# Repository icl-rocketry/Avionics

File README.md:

# Avionics
The main repository for hardware and software assosciated with the Ricardo Avionics Ecosystem. The goal of this project is to develop a generic highly configurable and powerful rocket avionics system which can accomodate many different rocket designs with differing propulsion systems as well as staging.

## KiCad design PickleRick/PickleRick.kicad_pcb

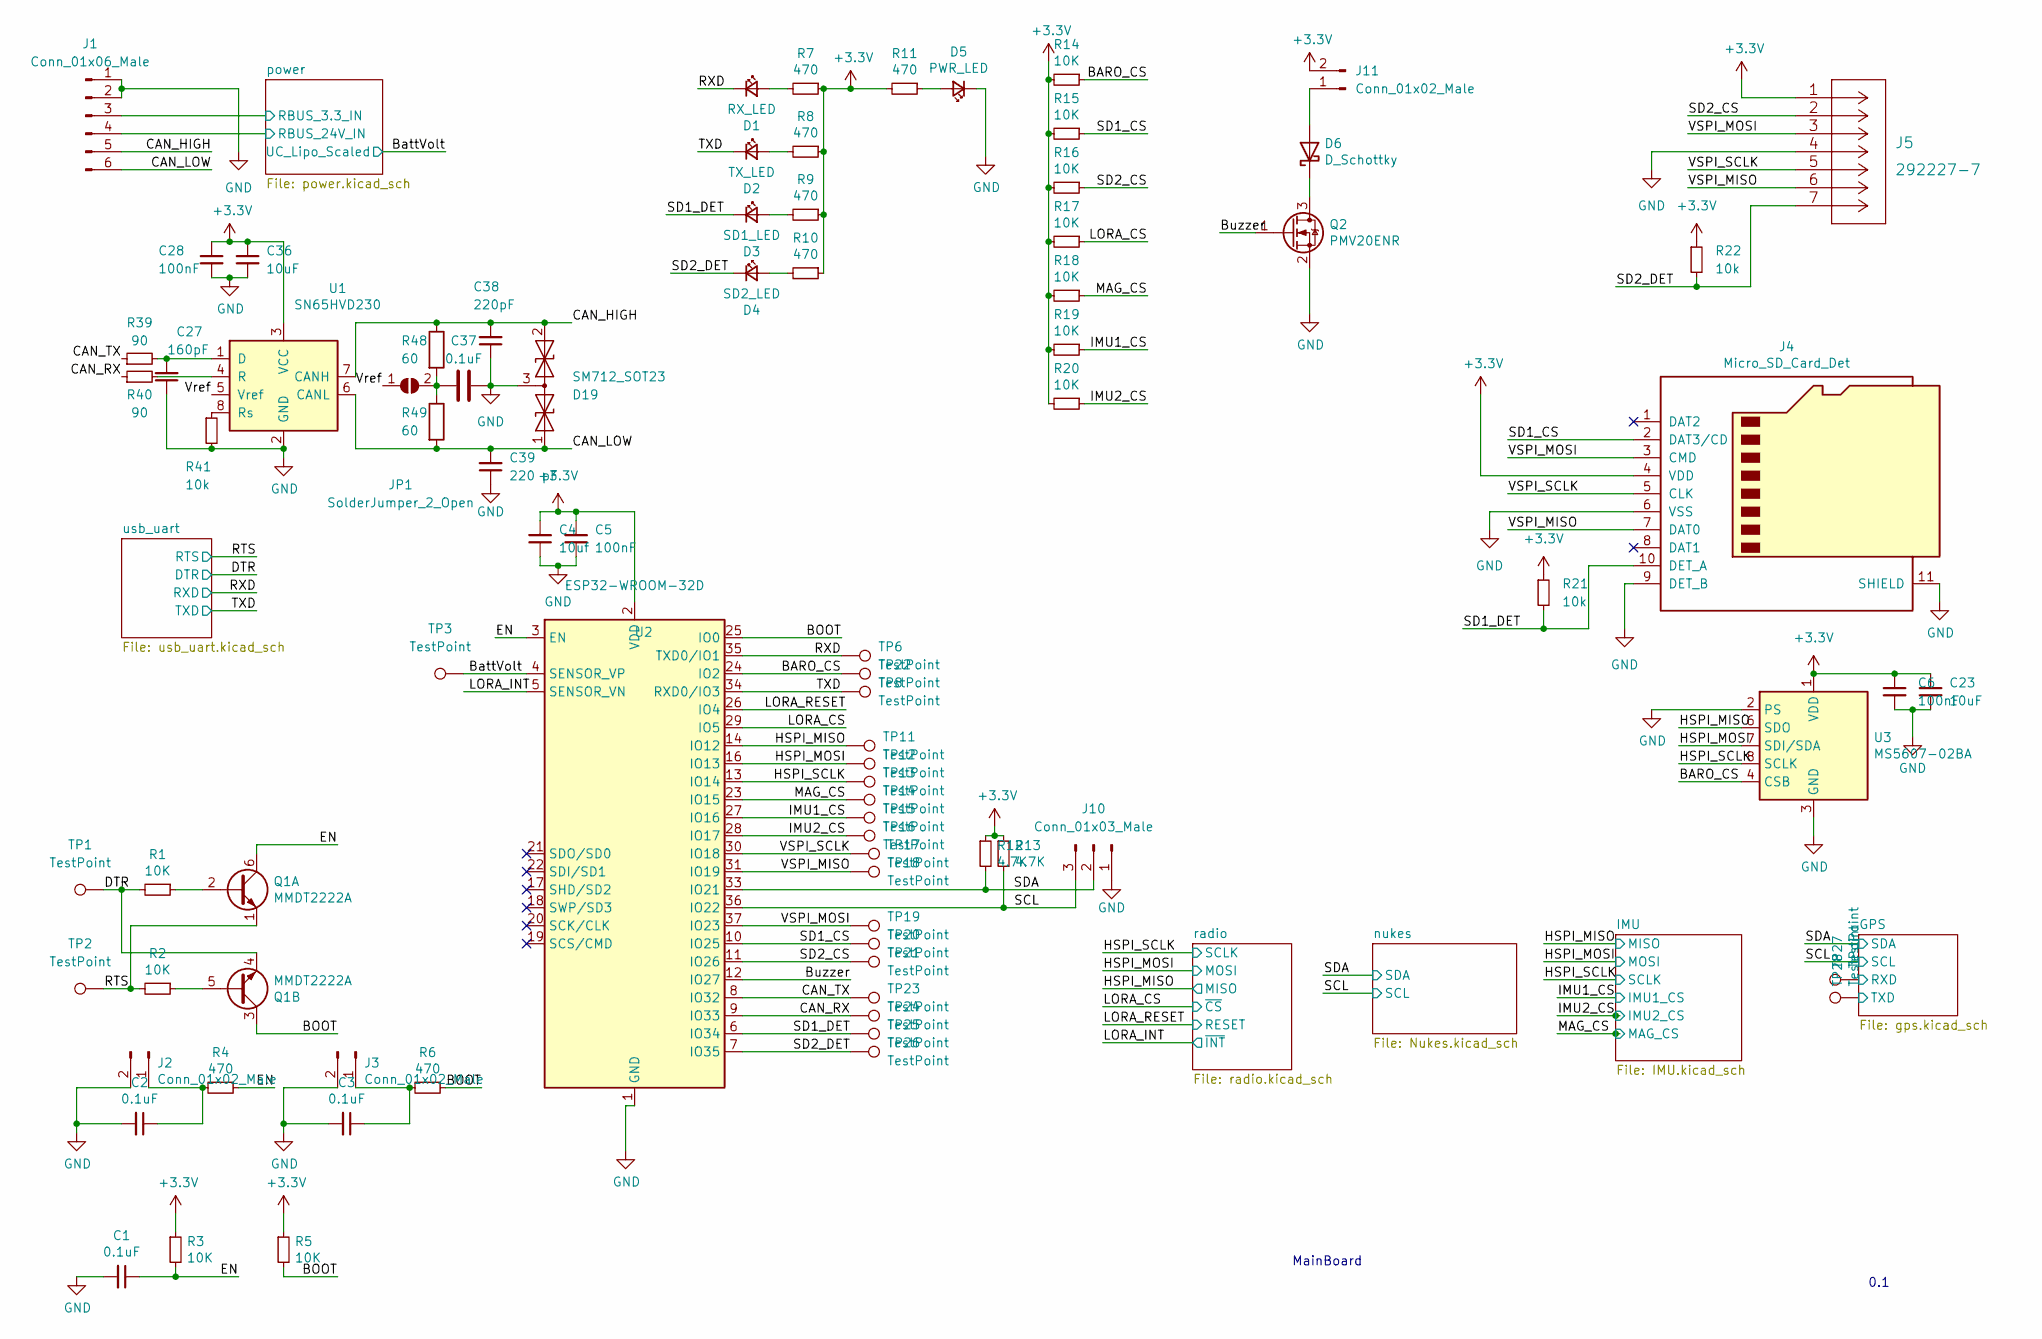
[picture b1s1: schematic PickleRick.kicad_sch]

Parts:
C1, C2, C3, C37: 0.1uF; C_0603_1608Metric
C4: 10uf; C_0603_1608Metric
C5, C6, C28: 100nF; C_0603_1608Metric
C23, C36: 10uF; C_0603_1608Metric
C27: 160pF; C_0603_1608Metric
C38: 220pF; C_0603_1608Metric
C39: 220 pF; C_0603_1608Metric
D1: RX_LED; LED_0603_1608Metric
D2: TX_LED; LED_0603_1608Metric
D3: SD1_LED; LED_0603_1608Metric
D4: SD2_LED; LED_0603_1608Metric
D5: PWR_LED; LED_0603_1608Metric
D6: D_Schottky; D_SOD-123F
D19: SM712_SOT23; SOT-23
J1: Conn_01x06_Male; Molex_Mini-Fit_Jr_5566-06A_2x03_P4.20mm_Vertical
J2, J3: Conn_01x02_Male; PinHeader_1x02_P2.54mm_Vertical
J4: Micro_SD_Card_Det; microSD_HC_Hirose_DM3AT-SF-PEJM5
J5: 292227-7
J10: Conn_01x03_Male; PinHeader_1x03_P2.54mm_Vertical
J11: Conn_01x02_Male; JST_PH_B2B-PH-K_1x02_P2.00mm_Vertical
JP1: SolderJumper_2_Open; SolderJumper-2_P1.3mm_Open_RoundedPad1.0x1.5mm
Q1: MMDT2222A; SOT-363_SC-70-6
Q2: PMV20ENR; SOT-23
R1, R2, R3, R5, R14, R15, R16, R17, R18, R19, R20: 10K; R_0603_1608Metric
R4, R6, R7, R8, R9, R10, R11: 470; R_0603_1608Metric
R12, R13: 4.7K; R_0603_1608Metric
R21, R22, R41: 10k; R_0603_1608Metric
R39, R40: 90; R_0603_1608Metric
R48, R49: 60; R_0603_1608Metric
TP1, TP2, TP3, TP6, TP8, TP11, TP12, TP13, TP14, TP15, TP16, TP17, TP18, TP19, TP20, TP21, TP22, TP23, TP24, TP25, TP26, TP27, TP28: TestPoint; TestPoint_Pad_D1.0mm
U1: SN65HVD230; SOIC-8_3.9x4.9mm_P1.27mm
U2: ESP32-WROOM-32D; ESP32-WROOM-32
U3: MS5607-02BA; LGA-8_3x5mm_P1.25mm

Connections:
/BARO_CS: R14.1, TP22.1, U2.24 (IO2), U3.4 (CSB), U3.5 (CSB)
/BOOT: Q1.3 (C2), R5.2, R6.1, U2.25 (IO0)
/BattVolt: TP3.1, U2.4 (SENSOR_VP); also elsewhere on the board
/Buzzer: Q2.1 (G), U2.12 (IO27)
/CAN_HIGH: C38.2, D19.2 (A2), J1.5, R48.1, U1.7 (CANH)
/CAN_LOW: C39.2, D19.1 (A1), J1.6, R49.2, U1.6 (CANL)
/CAN_RX: R40.1, TP24.1, U2.9 (IO33)
/CAN_TX: R39.1, TP23.1, U2.8 (IO32)
/DTR: Q1.4 (E2), R1.2, TP1.1; also elsewhere on the board
/EN: C1.1, Q1.6 (C1), R3.2, R4.1, U2.3 (EN)
/GPS/RXD: TP27.1; also elsewhere on the board
/GPS/TXD: TP28.1; also elsewhere on the board
/HSPI_MISO: TP11.1, U2.14 (IO12), U3.6 (SDO); also elsewhere on the board
/HSPI_MOSI: TP12.1, U2.16 (IO13), U3.7 (SDI/SDA); also elsewhere on the board
/HSPI_SCLK: TP13.1, U2.13 (IO14), U3.8 (SCLK); also elsewhere on the board
/IMU1_CS: R19.1, TP15.1, U2.27 (IO16); also elsewhere on the board
/IMU2_CS: R20.1, TP16.1, U2.28 (IO17); also elsewhere on the board
/LORA_CS: R17.1, U2.29 (IO5); also elsewhere on the board
/LORA_INT: U2.5 (SENSOR_VN); also elsewhere on the board
/LORA_RESET: U2.26 (IO4); also elsewhere on the board
/MAG_CS: R18.1, TP14.1, U2.23 (IO15); also elsewhere on the board
/RTS: Q1.1 (E1), R2.2, TP2.1; also elsewhere on the board
/RXD: D1.1 (K), TP6.1, U2.35 (TXD0/IO1); also elsewhere on the board
/SCL: J10.3, R13.2, U2.36 (IO22); also elsewhere on the board
/SD1_CS: J4.2 (DAT3/CD), R15.1, TP20.1, U2.10 (IO25)
/SD1_DET: D3.1 (K), J4.10 (DET_A), R21.2, TP25.1, U2.6 (IO34)
/SD2_CS: J5.2, R16.1, TP21.1, U2.11 (IO26)
/SD2_DET: D4.1 (K), J5.7, R22.2, TP26.1, U2.7 (IO35)
/SDA: J10.2, R12.2, U2.33 (IO21); also elsewhere on the board
/TXD: D2.1 (K), TP8.1, U2.34 (RXD0/IO3); also elsewhere on the board
/VSPI_MISO: J4.7 (DAT0), J5.6, TP18.1, U2.31 (IO19)
/VSPI_MOSI: J4.3 (CMD), J5.3, TP19.1, U2.37 (IO23)
/VSPI_SCLK: J4.5 (CLK), J5.5, TP17.1, U2.30 (IO18)
/Vref: JP1.1 (A), U1.5 (Vref)
/power/RBUS_3.3_IN: J1.3; also elsewhere on the board
/power/RBUS_24V_IN: J1.4; also elsewhere on the board
GND: C1.2, C2.2, C3.2, C4.1, C5.1, C6.2, C23.2, C27.1, C28.2, C36.2, C37.2, C38.1, C39.1, D5.1 (K), D19.3 (common), J1.1, J1.2, J2.2, J3.2, J4.6 (VSS), J4.9 (DET_B), J4.11 (SHIELD), J5.4, J10.1, Q2.2 (S), R41.2, U1.2 (GND), U2.1 (GND), U2.15 (GND), U2.38 (GND), U2.39 (GND), U3.2 (PS), U3.3 (GND); also elsewhere on the board
unnamed: C2.1, J2.1, R4.2
unnamed: C3.1, J3.1, R6.2
unnamed: C27.2, R39.2, U1.1 (D)
unnamed: C37.1, JP1.2 (B), R48.2, R49.1
unnamed: D1.2 (A), R7.2
unnamed: D2.2 (A), R8.2
unnamed: D3.2 (A), R9.2
unnamed: D4.2 (A), R10.2
unnamed: D5.2 (A), R11.1
unnamed: D6.1 (K), Q2.3 (D)
unnamed: D6.2 (A), J11.1
unnamed: Q1.2 (B1), R1.1
unnamed: Q1.5 (B2), R2.1
unnamed: R40.2, U1.4 (R)
unnamed: R41.1, U1.8 (Rs)

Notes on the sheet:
MainBoard
0.1

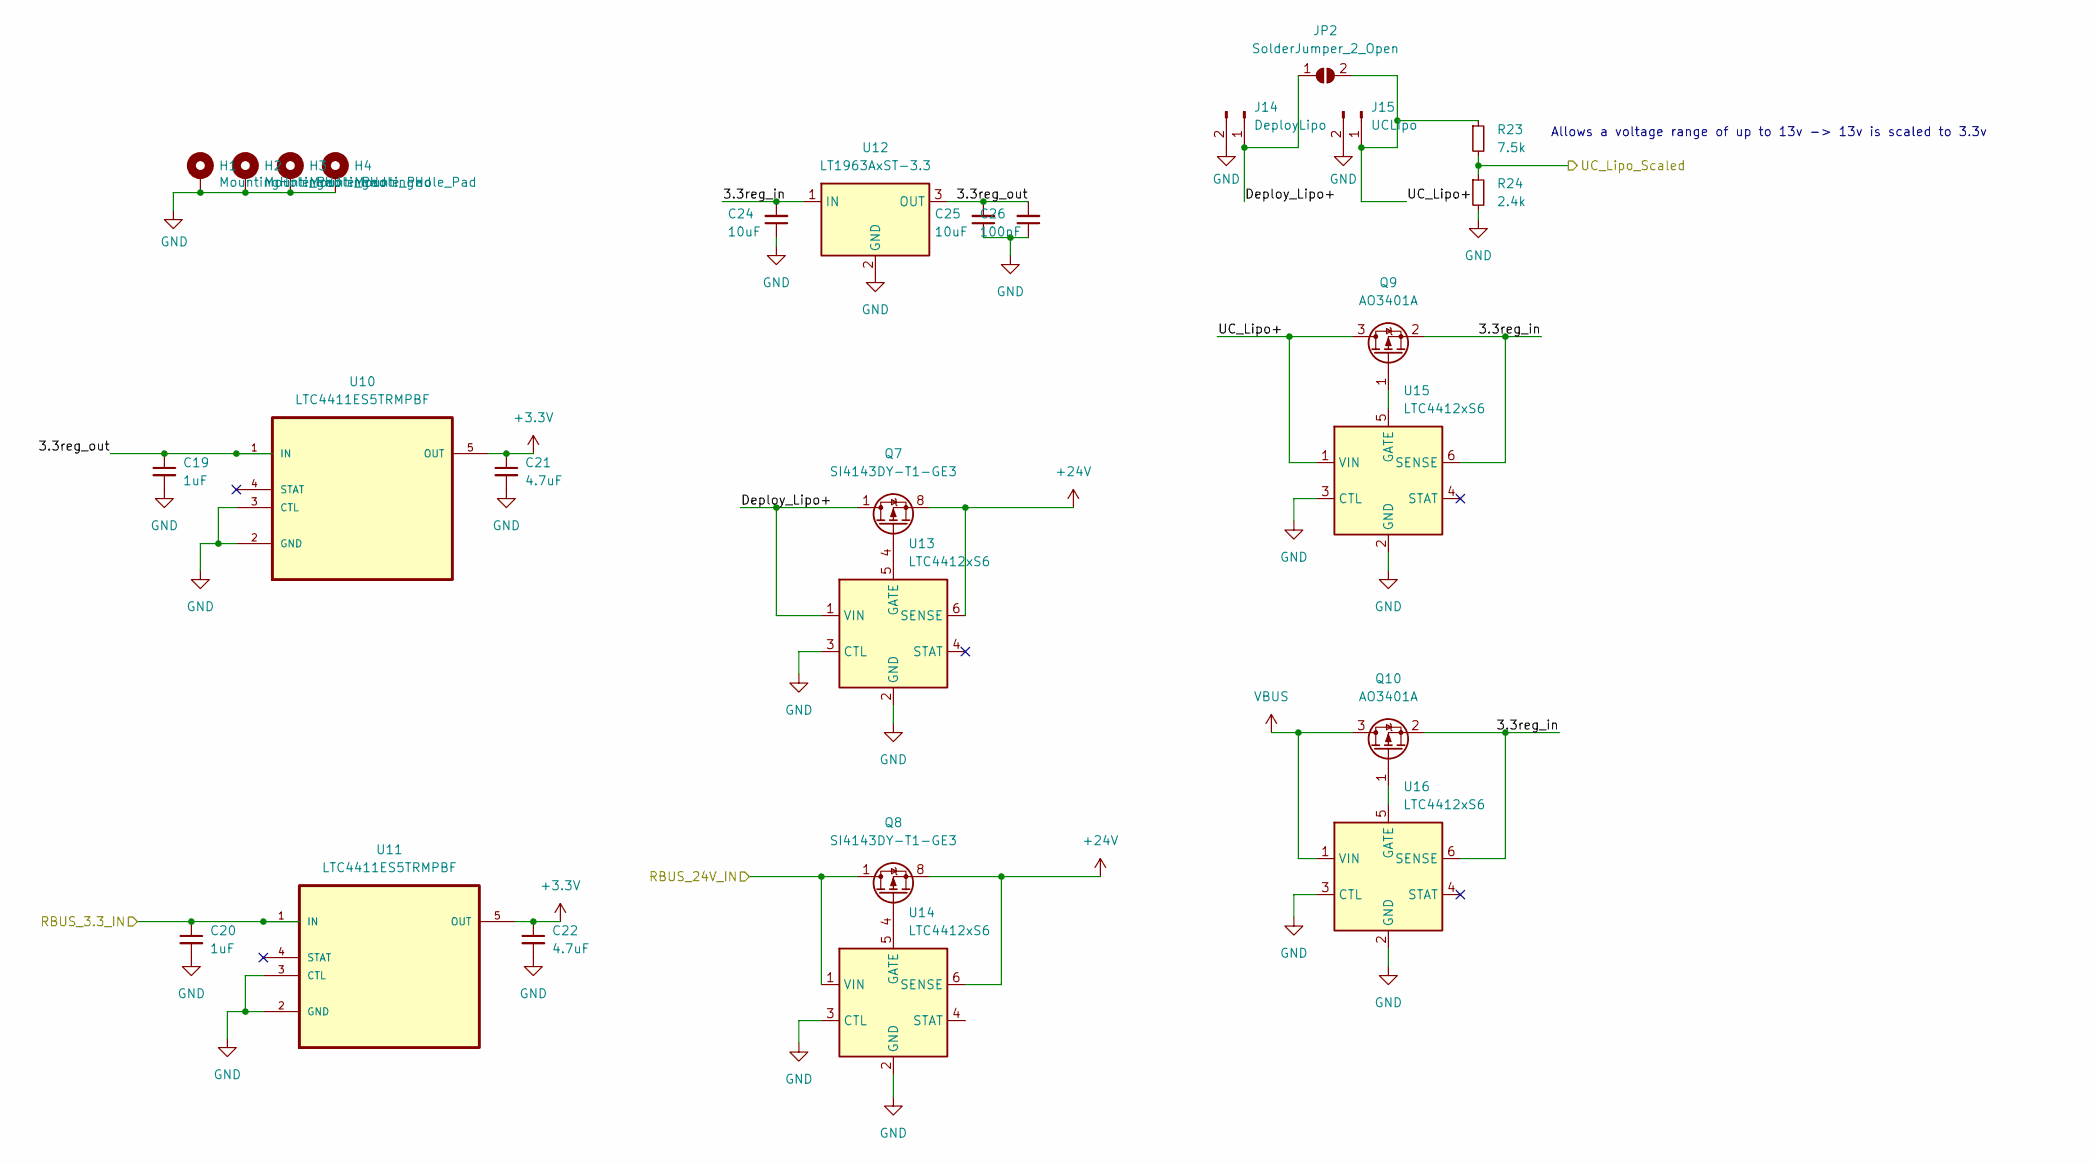
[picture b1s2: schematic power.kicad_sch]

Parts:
C19, C20: 1uF; C_0603_1608Metric
C21, C22: 4.7uF; C_0603_1608Metric
C24, C25: 10uF; C_0603_1608Metric
C26: 100nF; C_0603_1608Metric
H1, H2, H3, H4: MountingHole_Pad; MountingHole_3.2mm_M3_DIN965_Pad
J14: DeployLipo; TerminalBlock_Phoenix_MKDS-3-2-5.08_1x02_P5.08mm_Horizontal
J15: UCLipo; JST_PH_B2B-PH-K_1x02_P2.00mm_Vertical
JP2: SolderJumper_2_Open; SolderJumper-2_P1.3mm_Open_RoundedPad1.0x1.5mm
Q7, Q8: SI4143DY-T1-GE3; SOIC-8_3.9x4.9mm_P1.27mm
Q9, Q10: AO3401A; SOT-23
R23: 7.5k; R_0603_1608Metric
R24: 2.4k; R_0603_1608Metric
U10, U11: LTC4411ES5TRMPBF; SOT-23-5_HandSoldering; MPN LTC4411ES5#TRMPBF
U12: LT1963AxST-3.3; SOT-223-3_TabPin2
U13, U14, U15, U16: LTC4412xS6; TSOT-23-6

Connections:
+24V: Q7.5 (D), Q7.6 (D), Q7.7 (D), Q7.8 (D), Q8.5 (D), Q8.6 (D), Q8.7 (D), Q8.8 (D), U13.6 (SENSE), U14.6 (SENSE); also elsewhere on the board
/BattVolt: R23.2, R24.1; also elsewhere on the board
/power/3.3reg_in: C24.2, Q9.2 (S), Q10.2 (S), U12.1 (IN), U15.6 (SENSE), U16.6 (SENSE)
/power/3.3reg_out: C19.1, C25.2, C26.2, U10.1 (IN), U12.3 (OUT)
/power/Deploy_Lipo+: J14.1, JP2.1 (A), Q7.1 (S), Q7.2 (S), Q7.3 (S), U13.1 (VIN)
/power/RBUS_3.3_IN: C20.1, U11.1 (IN); also elsewhere on the board
/power/RBUS_24V_IN: Q8.1 (S), Q8.2 (S), Q8.3 (S), U14.1 (VIN); also elsewhere on the board
/power/UC_Lipo+: J15.1, JP2.2 (B), Q9.3 (D), R23.1, U15.1 (VIN)
GND: C19.2, C20.2, C21.2, C22.2, C24.1, C25.1, C26.1, H1.1, H2.1, H3.1, H4.1, J14.2, J15.2, R24.2, U10.2 (GND), U10.3 (CTL), U11.2 (GND), U11.3 (CTL), U12.2 (GND), U13.2 (GND), U13.3 (CTL), U14.2 (GND), U14.3 (CTL), U15.2 (GND), U15.3 (CTL), U16.2 (GND), U16.3 (CTL); also elsewhere on the board
unnamed: Q7.4 (G), U13.5 (GATE)
unnamed: Q8.4 (G), U14.5 (GATE)
unnamed: Q9.1 (G), U15.5 (GATE)
unnamed: Q10.1 (G), U16.5 (GATE)
VBUS: Q10.3 (D), U16.1 (VIN); also elsewhere on the board

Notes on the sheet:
Allows a voltage range of up to 13v -> 13v is scaled to 3.3v

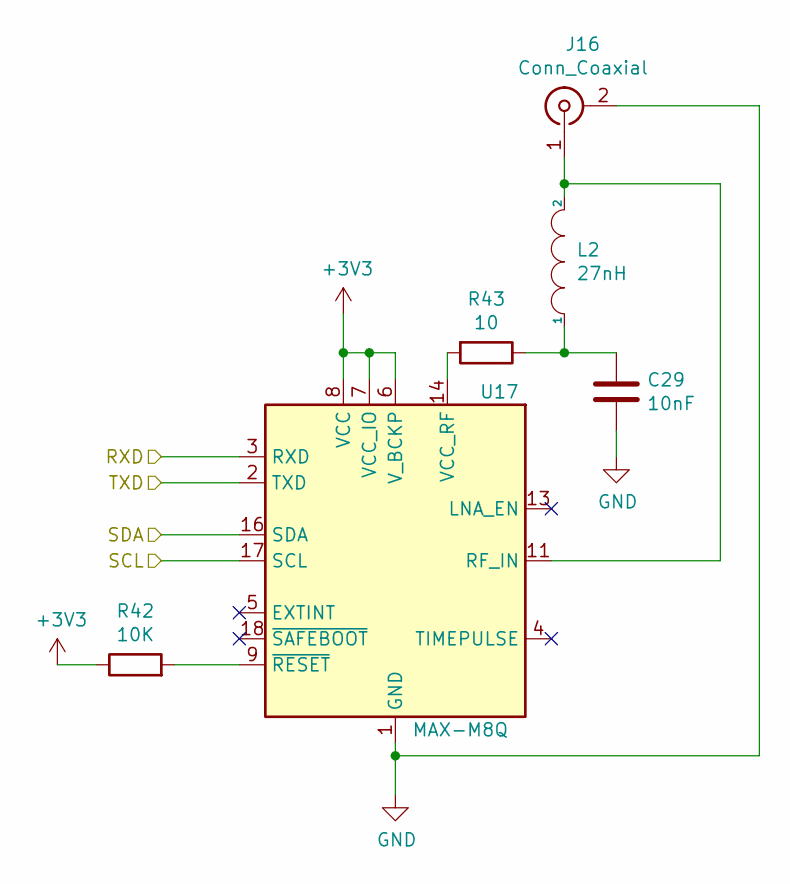
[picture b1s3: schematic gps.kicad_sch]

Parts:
C29: 10nF; C_0603_1608Metric
J16: Conn_Coaxial; SMA_Molex_73251-1153_EdgeMount_Horizontal
L2: 27nH; L_0603_1608Metric
R42: 10K; R_0603_1608Metric
R43: 10; R_0603_1608Metric
U17: MAX-M8Q; ublox_MAX

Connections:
/GPS/RXD: U17.3 (RXD); also elsewhere on the board
/GPS/TXD: U17.2 (TXD); also elsewhere on the board
/SCL: U17.17 (SCL); also elsewhere on the board
/SDA: U17.16 (SDA); also elsewhere on the board
GND: C29.2, J16.2 (Ext), U17.1 (GND), U17.10 (GND), U17.12 (GND); also elsewhere on the board
unnamed: C29.1, L2.1, R43.1
unnamed: J16.1 (In), L2.2, U17.11 (RF_IN)
unnamed: R42.2, U17.9 (~RESET)
unnamed: R43.2, U17.14 (VCC_RF)

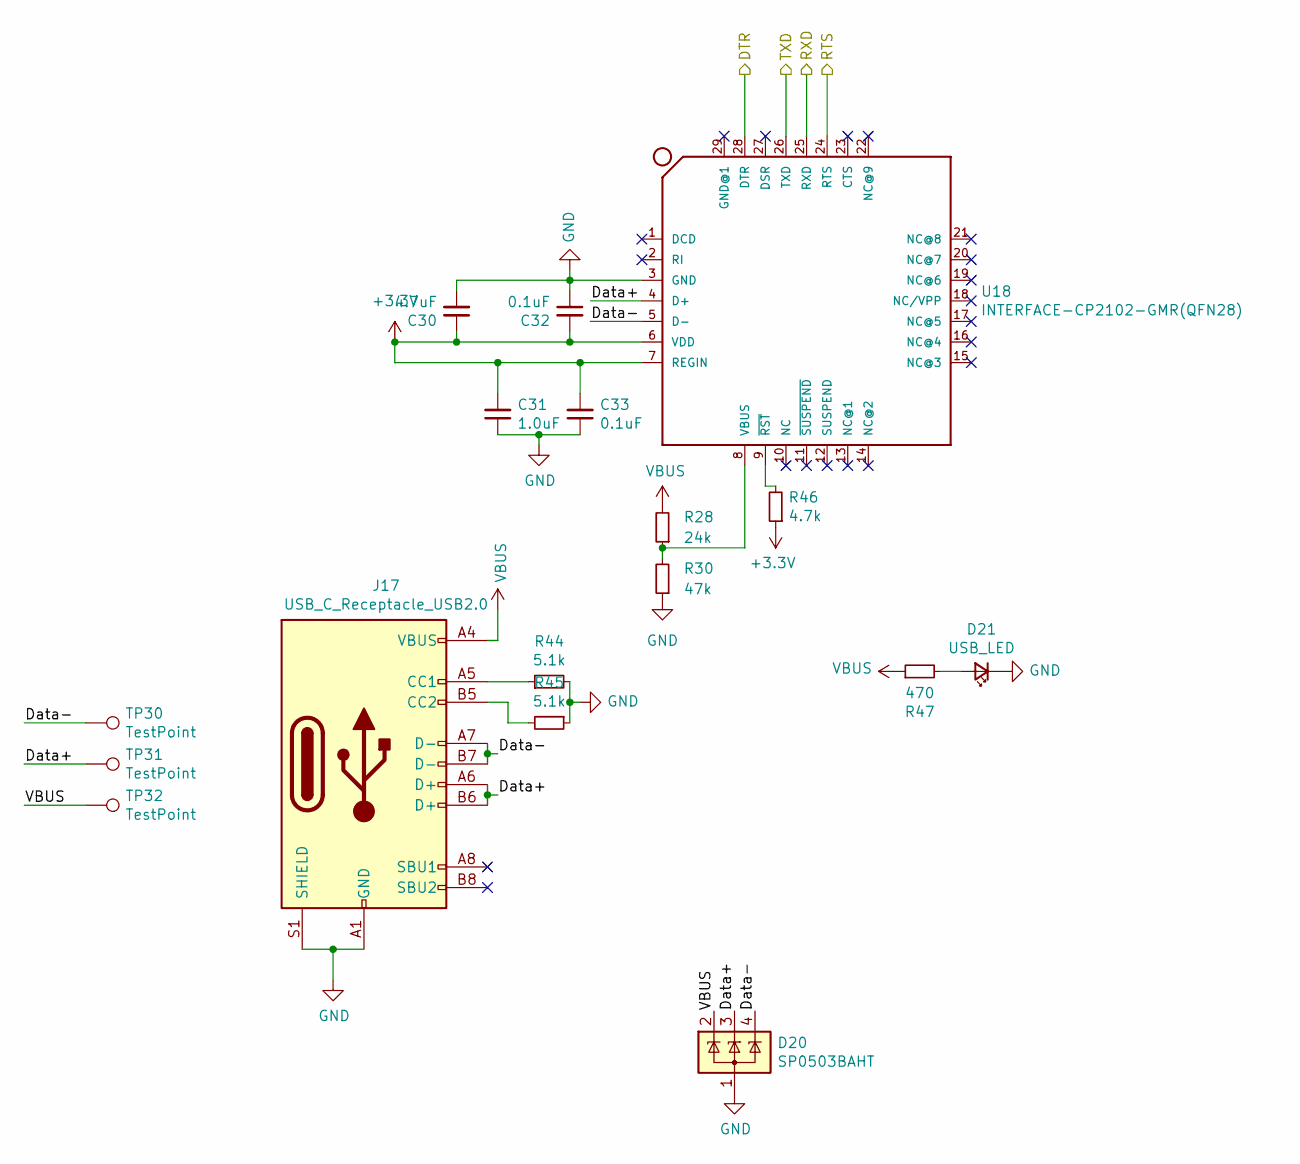
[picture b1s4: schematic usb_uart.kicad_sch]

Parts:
C30: 4.7uF; C_0603_1608Metric
C31: 1.0uF; C_0603_1608Metric
C32, C33: 0.1uF; C_0603_1608Metric
D20: SP0503BAHT; SOT-143
D21: USB_LED; LED_0603_1608Metric
J17: USB_C_Receptacle_USB2.0; USB_C_Receptacle_GCT_USB4085
R28: 24k; R_0603_1608Metric
R30: 47k; R_0603_1608Metric
R44, R45: 5.1k; R_0603_1608Metric
R46: 4.7k; R_0603_1608Metric
R47: 470; R_0603_1608Metric
TP30, TP31, TP32: TestPoint; TestPoint_Pad_D1.0mm
U18: INTERFACE-CP2102-GMR(QFN28); QFN28G_0.5-5X5MM; MPN CP2102-GMR

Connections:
/DTR: U18.28 (DTR); also elsewhere on the board
/RTS: U18.24 (RTS); also elsewhere on the board
/RXD: U18.25 (RXD); also elsewhere on the board
/TXD: U18.26 (TXD); also elsewhere on the board
/usb_uart/Data+: D20.3 (K), J17.A6 (D+), J17.B6 (D+), TP31.1, U18.4 (D+)
/usb_uart/Data-: D20.4 (K), J17.A7 (D-), J17.B7 (D-), TP30.1, U18.5 (D-)
GND: C30.2, C31.1, C32.1, C33.1, D20.1 (A), D21.1 (K), J17.A1 (GND), J17.A12 (GND), J17.B1 (GND), J17.B12 (GND), J17.S1 (SHIELD), R30.1, R44.2, R45.1, U18.3 (GND); also elsewhere on the board
unnamed: D21.2 (A), R47.2
unnamed: J17.A5 (CC1), R44.1
unnamed: J17.B5 (CC2), R45.2
unnamed: R28.1, R30.2, U18.8 (VBUS)
unnamed: R46.2, U18.9 (~RST)
VBUS: D20.2 (K), J17.A4 (VBUS), J17.A9 (VBUS), J17.B4 (VBUS), J17.B9 (VBUS), R28.2, R47.1, TP32.1; also elsewhere on the board

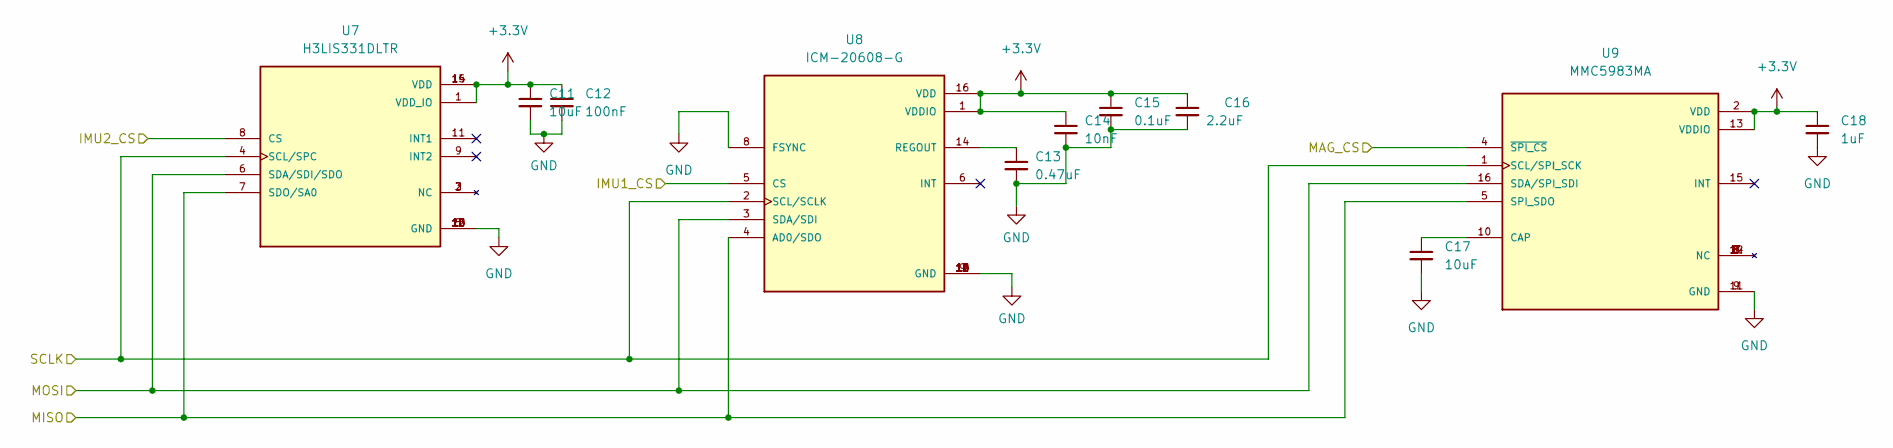
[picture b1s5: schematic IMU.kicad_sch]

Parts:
C11, C17: 10uF; C_0603_1608Metric
C12: 100nF; C_0603_1608Metric
C13: 0.47uF; C_0603_1608Metric
C14: 10nF; C_0603_1608Metric
C15: 0.1uF; C_0603_1608Metric
C16: 2.2uF; C_0603_1608Metric
C18: 1uF; C_0603_1608Metric
U7: H3LIS331DLTR; PQFN50P300X300X100-16N; PARTREV 2
U8: ICM-20608-G; PQFN50P300X300X80-16N; PARTREV 1.0
U9: MMC5983MA; PQFN50P300X300X100-16N; PARTREV A

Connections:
/HSPI_MISO: U7.7 (SDO/SA0), U8.4 (AD0/SDO), U9.5 (SPI_SDO); also elsewhere on the board
/HSPI_MOSI: U7.6 (SDA/SDI/SDO), U8.3 (SDA/SDI), U9.16 (SDA/SPI_SDI); also elsewhere on the board
/HSPI_SCLK: U7.4 (SCL/SPC), U8.2 (SCL/SCLK), U9.1 (SCL/SPI_SCK); also elsewhere on the board
/IMU1_CS: U8.5 (CS); also elsewhere on the board
/IMU2_CS: U7.8 (CS); also elsewhere on the board
/MAG_CS: U9.4 (~SPI_CS); also elsewhere on the board
GND: C11.2, C12.2, C13.2, C14.2, C15.2, C16.2, C17.2, C18.2, U7.5 (GND), U7.10 (GND), U7.12 (GND), U7.13 (GND), U7.16 (GND), U8.8 (FSYNC), U8.9 (GND), U8.10 (GND), U8.11 (GND), U8.12 (GND), U8.13 (GND), U8.15 (GND), U9.9 (GND), U9.11 (GND); also elsewhere on the board
unnamed: C13.1, U8.14 (REGOUT)
unnamed: C17.1, U9.10 (CAP)

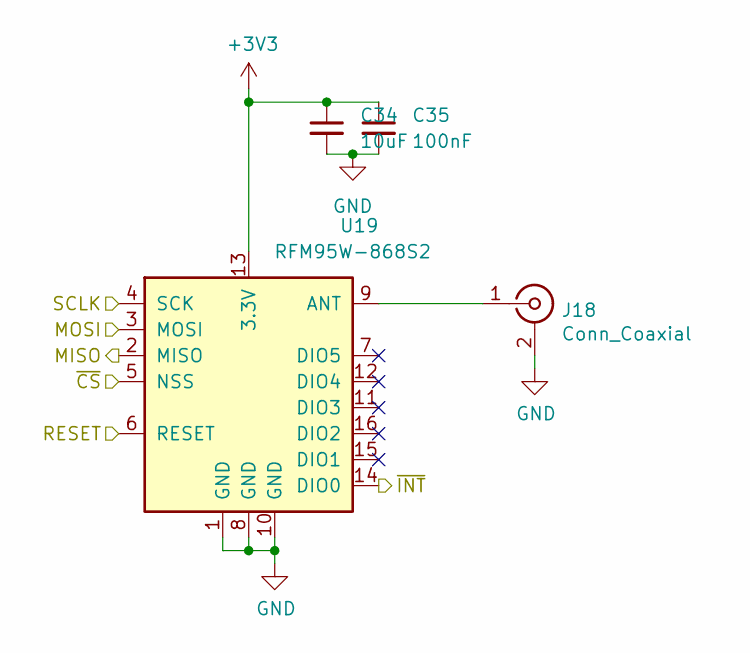
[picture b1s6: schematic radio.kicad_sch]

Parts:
C34: 10uF; C_0603_1608Metric
C35: 100nF; C_0603_1608Metric
J18: Conn_Coaxial; SMA_Molex_73251-1153_EdgeMount_Horizontal
U19: RFM95W-868S2; HOPERF_RFM9XW_SMD

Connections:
/HSPI_MISO: U19.2 (MISO); also elsewhere on the board
/HSPI_MOSI: U19.3 (MOSI); also elsewhere on the board
/HSPI_SCLK: U19.4 (SCK); also elsewhere on the board
/LORA_CS: U19.5 (NSS); also elsewhere on the board
/LORA_INT: U19.14 (DIO0); also elsewhere on the board
/LORA_RESET: U19.6 (RESET); also elsewhere on the board
GND: C34.2, C35.2, J18.2 (Ext), U19.1 (GND), U19.8 (GND), U19.10 (GND); also elsewhere on the board
unnamed: J18.1 (In), U19.9 (ANT)

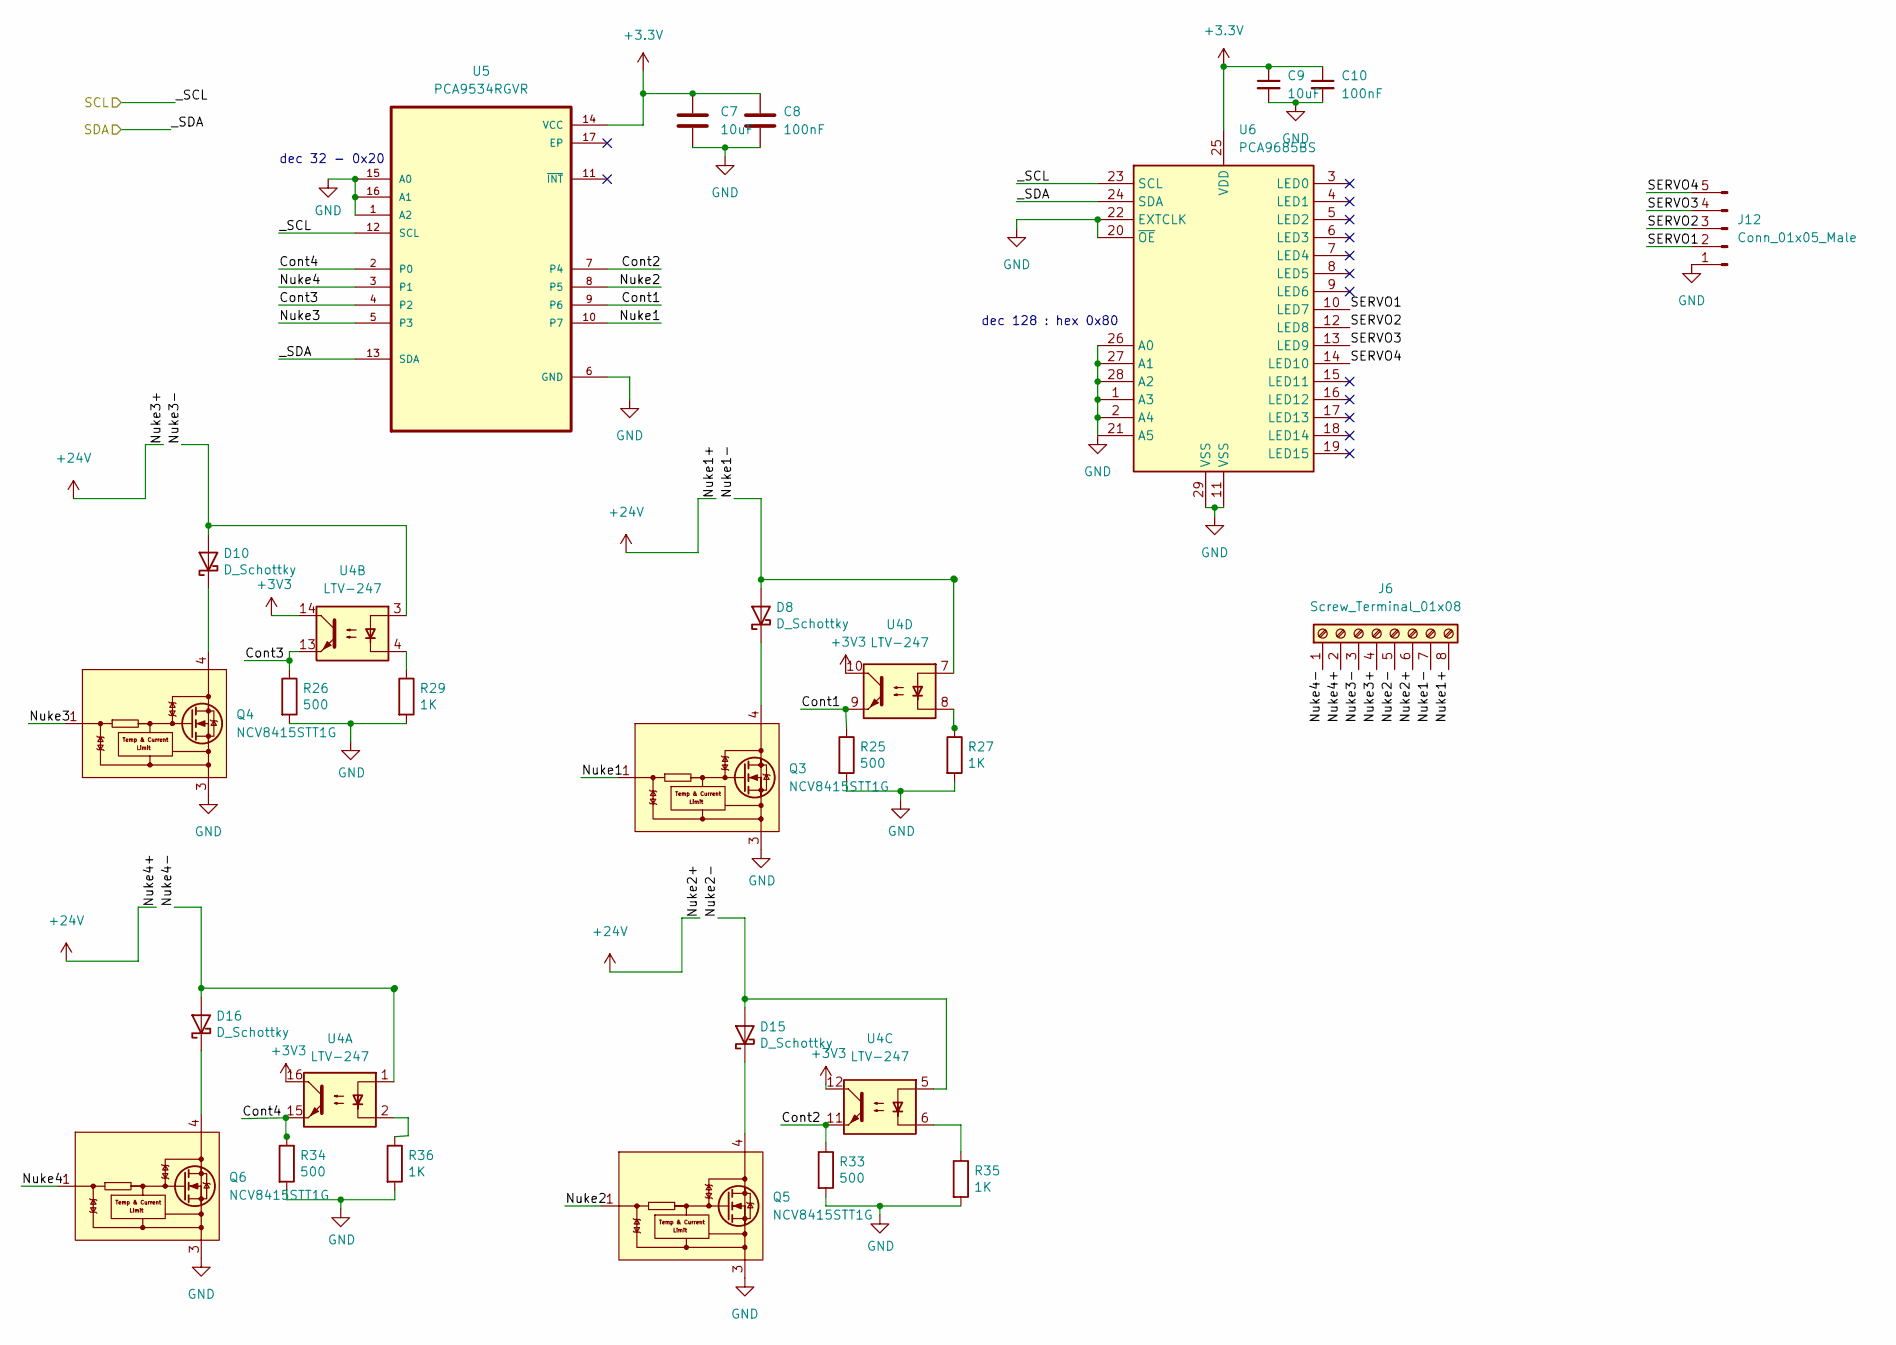
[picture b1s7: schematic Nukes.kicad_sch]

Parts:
C7, C9: 10uF; C_0603_1608Metric
C8, C10: 100nF; C_0603_1608Metric
D8, D10, D15, D16: D_Schottky; D_SOD-128
J6: Screw_Terminal_01x08; TerminalBlock_TE_282834-8_1x08_P2.54mm_Horizontal
J12: Conn_01x05_Male; PinHeader_1x05_P2.54mm_Vertical
Q3, Q4, Q5, Q6: NCV8415STT1G; SOT-223
R25, R26, R33, R34: 500; R_0603_1608Metric
R27, R29, R35, R36: 1K; R_0603_1608Metric
U4: LTV-247; SOP-16_4.4x10.4mm_P1.27mm
U5: PCA9534RGVR; QFN65P400X400X100-17N
U6: PCA9685BS; QFN-28-1EP_6x6mm_P0.65mm_EP4.25x4.25mm

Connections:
+24V: J6.2, J6.4, J6.6, J6.8; also elsewhere on the board
/SCL: U5.12 (SCL), U6.23 (SCL); also elsewhere on the board
/SDA: U5.13 (SDA), U6.24 (SDA); also elsewhere on the board
/nukes/Cont1: R25.1, U4.9, U5.9 (P6)
/nukes/Cont2: R33.1, U4.11, U5.7 (P4)
/nukes/Cont3: R26.1, U4.13, U5.4 (P2)
/nukes/Cont4: R34.1, U4.15, U5.2 (P0)
/nukes/Nuke1: Q3.1 (G), U5.10 (P7)
/nukes/Nuke1-: D8.2 (A), J6.7, U4.7
/nukes/Nuke2: Q5.1 (G), U5.8 (P5)
/nukes/Nuke2-: D15.2 (A), J6.5, U4.5
/nukes/Nuke3: Q4.1 (G), U5.5 (P3)
/nukes/Nuke3-: D10.2 (A), J6.3, U4.3
/nukes/Nuke4: Q6.1 (G), U5.3 (P1)
/nukes/Nuke4-: D16.2 (A), J6.1, U4.1
/nukes/SERVO1: J12.2, U6.10 (LED7)
/nukes/SERVO2: J12.3, U6.12 (LED8)
/nukes/SERVO3: J12.4, U6.13 (LED9)
/nukes/SERVO4: J12.5, U6.14 (LED10)
GND: C7.2, C8.2, C9.2, C10.2, J12.1, Q3.3 (S), Q4.3 (S), Q5.3 (S), Q6.3 (S), R25.2, R26.2, R27.2, R29.2, R33.2, R34.2, R35.2, R36.2, U5.1 (A2), U5.6 (GND), U5.15 (A0), U5.16 (A1), U6.1 (A3), U6.2 (A4), U6.11 (VSS), U6.20 (~OE), U6.21 (A5), U6.22 (EXTCLK), U6.26 (A0), U6.27 (A1), U6.28 (A2), U6.29 (VSS); also elsewhere on the board
unnamed: D8.1 (K), Q3.2 (D), Q3.4 (D)
unnamed: D10.1 (K), Q4.2 (D), Q4.4 (D)
unnamed: D15.1 (K), Q5.2 (D), Q5.4 (D)
unnamed: D16.1 (K), Q6.2 (D), Q6.4 (D)
unnamed: R27.1, U4.8
unnamed: R29.1, U4.4
unnamed: R35.1, U4.6
unnamed: R36.1, U4.2

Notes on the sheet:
dec 32 - 0x20
dec 128 : hex 0x80

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
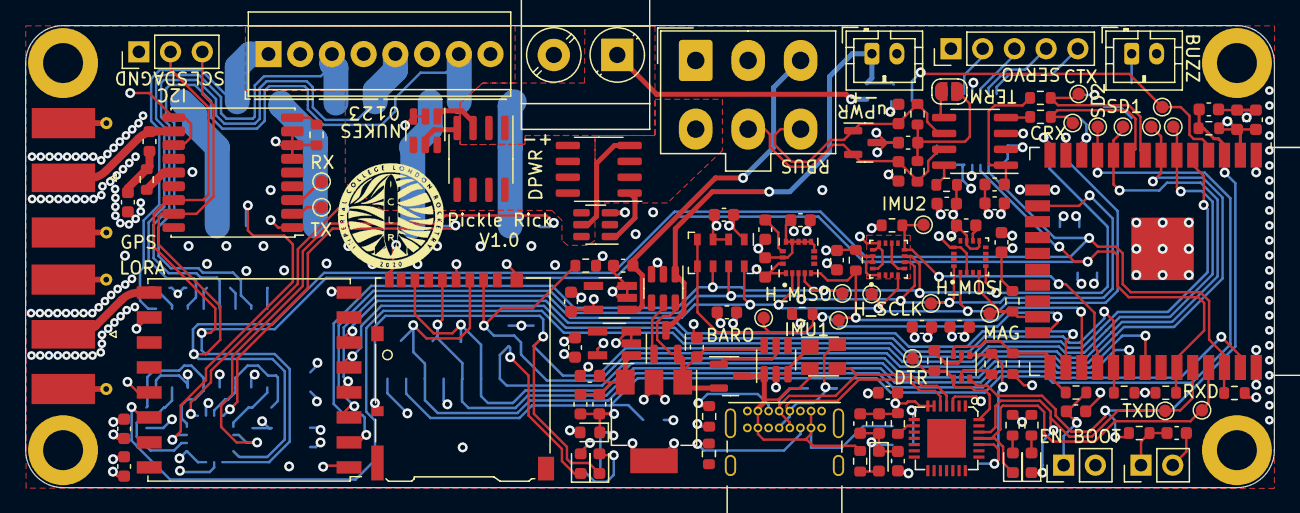
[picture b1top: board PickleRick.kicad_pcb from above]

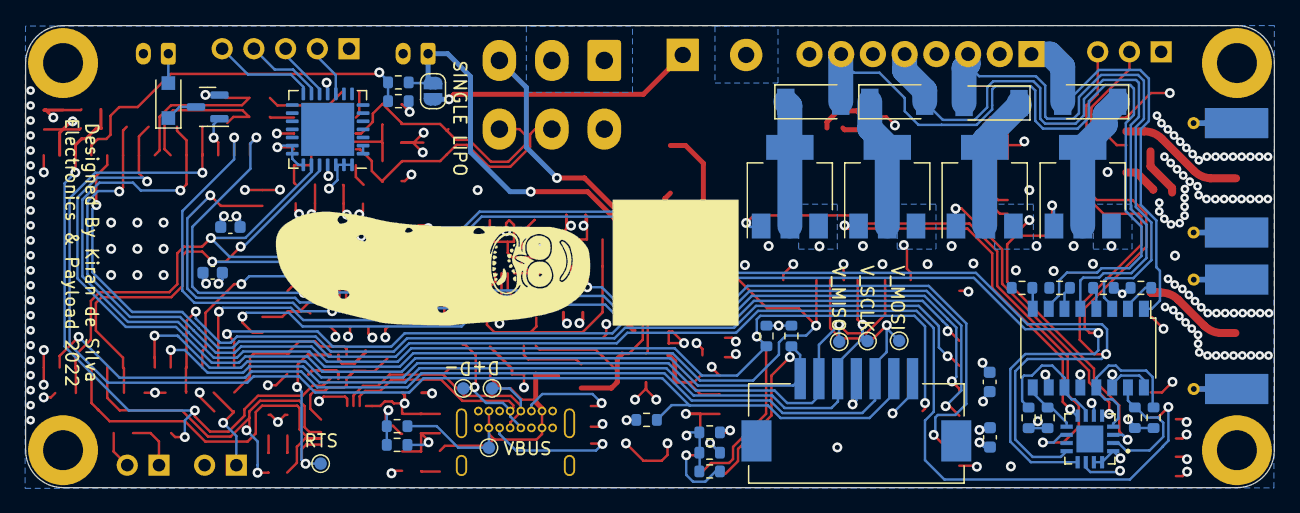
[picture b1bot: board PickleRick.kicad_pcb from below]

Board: 4 copper layers, 100.0 x 37.0 mm, 174 parts (44 on the bottom side), 101 nets.

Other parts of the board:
LOGO1: LOGO; iclr_logo

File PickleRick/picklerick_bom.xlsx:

Id | Designator | Package | Quantity | Designation | Supplier and ref
4 | C1 | C_0603_1608Metric | 1 | 1nF
10 | C11,C23,C24,C34,C17,C25,C36,C9,C7 | C_0603_1608Metric | 9 | 10uF
27 | C13 | C_0603_1608Metric | 1 | 0.47uF
20 | C15,C32,C37,C33,C2,C3 | C_0603_1608Metric | 6 | 0.1uF
58 | C16 | C_0603_1608Metric | 1 | 2.2uF
32 | C18,C20,C19 | C_0603_1608Metric | 3 | 1uF
46 | C22,C21 | C_0603_1608Metric | 2 | 4.7uF
64 | C27 | C_0603_1608Metric | 1 | 160pF
26 | C29,C14 | C_0603_1608Metric | 2 | 10nF
7 | C30 | CP_Elec_3x5.3 | 1 | 4.7uF
61 | C31 | C_0603_1608Metric | 1 | 1.0uF
48 | C38 | C_0603_1608Metric | 1 | 220pF
63 | C39 | C_0603_1608Metric | 1 | 220 pF
54 | C4 | C_0603_1608Metric | 1 | 10uf
5 | C5,C35,C6,C26,C12,C28,C8,C10 | C_0603_1608Metric | 8 | 100nF
8 | D1 | LED_0603_1608Metric | 1 | RX_LED
52 | D19 | SOT-23 | 1 | SM712_SOT23
44 | D2 | LED_0603_1608Metric | 1 | TX_LED
30 | D20 | SOT-143 | 1 | SP0503BAHT
47 | D21 | LED_0603_1608Metric | 1 | USB_LED
14 | D3 | LED_0603_1608Metric | 1 | SD1_LED
39 | D4 | LED_0603_1608Metric | 1 | SD2_LED
59 | D5 | LED_0603_1608Metric | 1 | PWR_LED
75 | D6 | D_SOD-123F | 1 | D_Schottky
71 | D8,D10,D16,D15 | D_SOD-128 | 4 | D_Schottky
76 | G*** | pickle_ric | 1 | LOGO
33 | H3,H4,H1,H2 | MountingHole_3.2mm_M3_DIN965_Pad | 4 | MountingHole_Pad
34 | J1 | Molex_Mini-Fit_Jr_5566-06A_2x03_P4.20mm_Vertical | 1 | Conn_01x06_Male
28 | J10 | PinHeader_1x03_P2.54mm_Vertical | 1 | Conn_01x03_Male
35 | J11 | JST_PH_B2B-PH-K_1x02_P2.00mm_Vertical | 1 | Conn_01x02_Male
37 | J12 | PinHeader_1x05_P2.54mm_Vertical | 1 | Conn_01x05_Male
56 | J14 | TerminalBlock_Phoenix_MKDS-3-2-5.08_1x02_P5.08mm_Horizontal | 1 | DeployLipo
51 | J15 | JST_PH_B2B-PH-K_1x02_P2.00mm_Vertical | 1 | UCLipo
36 | J17 | USB_C_Receptacle_GCT_USB4085 | 1 | USB_C_Receptacle_USB2.0
21 | J18,J16 | SMA_Molex_73251-1153_EdgeMount_Horizontal | 2 | Conn_Coaxial
15 | J3,J2 | PinHeader_1x02_P2.54mm_Vertical | 2 | Conn_01x02_Male
12 | J4 | microSD_HC_Hirose_DM3AT-SF-PEJM5 | 1 | Micro_SD_Card_Det
1 | J5 | 292227-7 | 1 | CON7_1X7_DRH_HPI125_TYC
25 | J6 | TerminalBlock_TE_282834-8_1x08_P2.54mm_Horizontal | 1 | Screw_Terminal_01x08
16 | JP1,JP2 | SolderJumper-2_P1.3mm_Open_RoundedPad1.0x1.5mm | 2 | SolderJumper_2_Open
60 | L2 | L_0603_1608Metric | 1 | 27nH
23 | LOGO1 | iclr_logo | 1 | LOGO
62 | Q1 | SOT-363_SC-70-6 | 1 | MMDT2222A
17 | Q10,Q9 | SOT-23 | 2 | AO3401A
78 | Q2 | SOT-23 | 1 | PMV20ENR
69 | Q4,Q6,Q3,Q5 | SOT-223 | 4 | NCV8415STT1G
13 | Q7,Q8 | SOIC-8_3.9x4.9mm_P1.27mm | 2 | SI4143DY-T1-GE3
53 | R12,R13 | R_0603_1608Metric | 2 | 4.7K
68 | R23 | R_0603_1608Metric | 1 | 7.5k
77 | R24 | R_0603_1608Metric | 1 | 2.4k
67 | R27,R36,R29,R35 | R_0603_1608Metric | 4 | 1K
74 | R28 | R_0603_1608Metric | 1 | 24k
72 | R30 | R_0603_1608Metric | 1 | 47k
66 | R33,R25,R26,R34 | R_0603_1608Metric | 4 | 500
31 | R40,R39 | R_0603_1608Metric | 2 | 90
24 | R41,R21,R22 | R_0603_1608Metric | 3 | 10k
2 | R42,R3,R1,R17,R15,R20,R5,R19,R18,R2,R14,R16 | R_0603_1608Metric | 12 | 10K
11 | R43 | R_0603_1608Metric | 1 | 10
45 | R45,R44 | R_0603_1608Metric | 2 | 5.1k
42 | R46 | R_0603_1608Metric | 1 | 4.7k
3 | R49,R48 | R_0603_1608Metric | 2 | 60
18 | R7,R47,R4,R6,R8,R10,R9,R11 | R_0603_1608Metric | 8 | 470
49 | REF** | Write_Pad | 1 | Write_Pad
6 | TP22,TP1,TP25,TP27,TP13,TP16,TP28,TP14,TP15,TP24,TP12,TP26,TP6,TP21,TP3,TP23,TP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 | TestPoint_Pad_D1.0mm | 26 | TestPoint
40 | U1 | SOIC-8_3.9x4.9mm_P1.27mm | 1 | SN65HVD230
29 | U11,U10 | SOT-23-5_HandSoldering | 2 | LTC4411ES5TRMPBF
65 | U12 | SOT-223-3_TabPin2 | 1 | LT1963AxST-3.3
19 | U15,U13,U14,U16 | TSOT-23-6 | 4 | LTC4412xS6
9 | U17 | ublox_MAX | 1 | MAX-M8Q
38 | U18 | QFN28G_0.5-5X5MM | 1 | INTERFACE-CP2102-GMR(QFN28)
43 | U19 | HOPERF_RFM9XW_SMD | 1 | RFM95W-868S2
22 | U2 | ESP32-WROOM-32 | 1 | ESP32-WROOM-32D
57 | U3 | LGA-8_3x5mm_P1.25mm | 1 | MS5607-02BA
73 | U4 | SOP-16_4.4x10.4mm_P1.27mm | 1 | LTV-247
79 | U5 | QFN65P400X400X100-17N | 1 | PCA9534RGVR
70 | U6 | QFN-28-1EP_6x6mm_P0.65mm_EP4.25x4.25mm | 1 | PCA9685BS
41 | U7 | PQFN50P300X300X100-16N | 1 | H3LIS100DLTR
50 | U8 | PQFN50P300X300X80-16N | 1 | ICM-20608-G
55 | U9 | PQFN50P300X300X100-16N | 1 | MMC5983MA

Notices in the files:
parts and their libraries:
Copyright 2021 Accelerated Designs. All rights reserved.
